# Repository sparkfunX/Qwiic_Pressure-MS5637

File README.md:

SparkFun Qwiic Pressure with MS5637
========================================

[*SparkX Pressure Sensor (Qwiic) - MS5637 (SPX-14688)*](https://www.sparkfun.com/products/14688)

MEMs based barometric pressure sensors are quite common these days. The Qwiic Pressure Sensor with the MS5637 shines by being the most sensitive barometric pressure sensor we have come across. It is capable of detecting the difference in 13cm of air! And the MS5637 is low cost and easy to use.

The Qwiic Pressure Sensor for the MS5637 is a very sensitive, fully calibrated, low power, easy to use barometric pressure sensor capable of detecting a change of as little as 13cm of air! The Qwiic Pressure Sensor is perfect for home weather stations, detecting changes in altitude, and pneumatic based switches or actuators.

The original manufacturer TE has written a great Arduino library for the device. We've added a heap of examples and new functions to make the sensor even easier to use. Search the Arduino Library manager for 'SparkFun MS5637' to get the latest library features.

SparkFun labored with love to create this code. Feel like supporting open source hardware? 
Buy a [breakout board](https://www.sparkfun.com/products/14688) from SparkFun!

Repository Contents
-------------------

* **/Documents** - Datasheets
* **/Hardware** - Eagle design files (.brd, .sch)

Library
--------------
* **[Arduino Library](https://github.com/sparkfun/SparkFun_MS5637_Arduino_Library)** - Library for reading pressure in mBar, altitude, etc.

License Information
-------------------

This product is _**open source**_! 

If you have any questions or concerns on licensing, please contact techsupport@sparkfun.com.

Please use, reuse, and modify these files as you see fit. Please maintain attribution to SparkFun Electronics and release any derivative under the same license.

Distributed as-is; no warranty is given.

- Your friends at SparkFun.

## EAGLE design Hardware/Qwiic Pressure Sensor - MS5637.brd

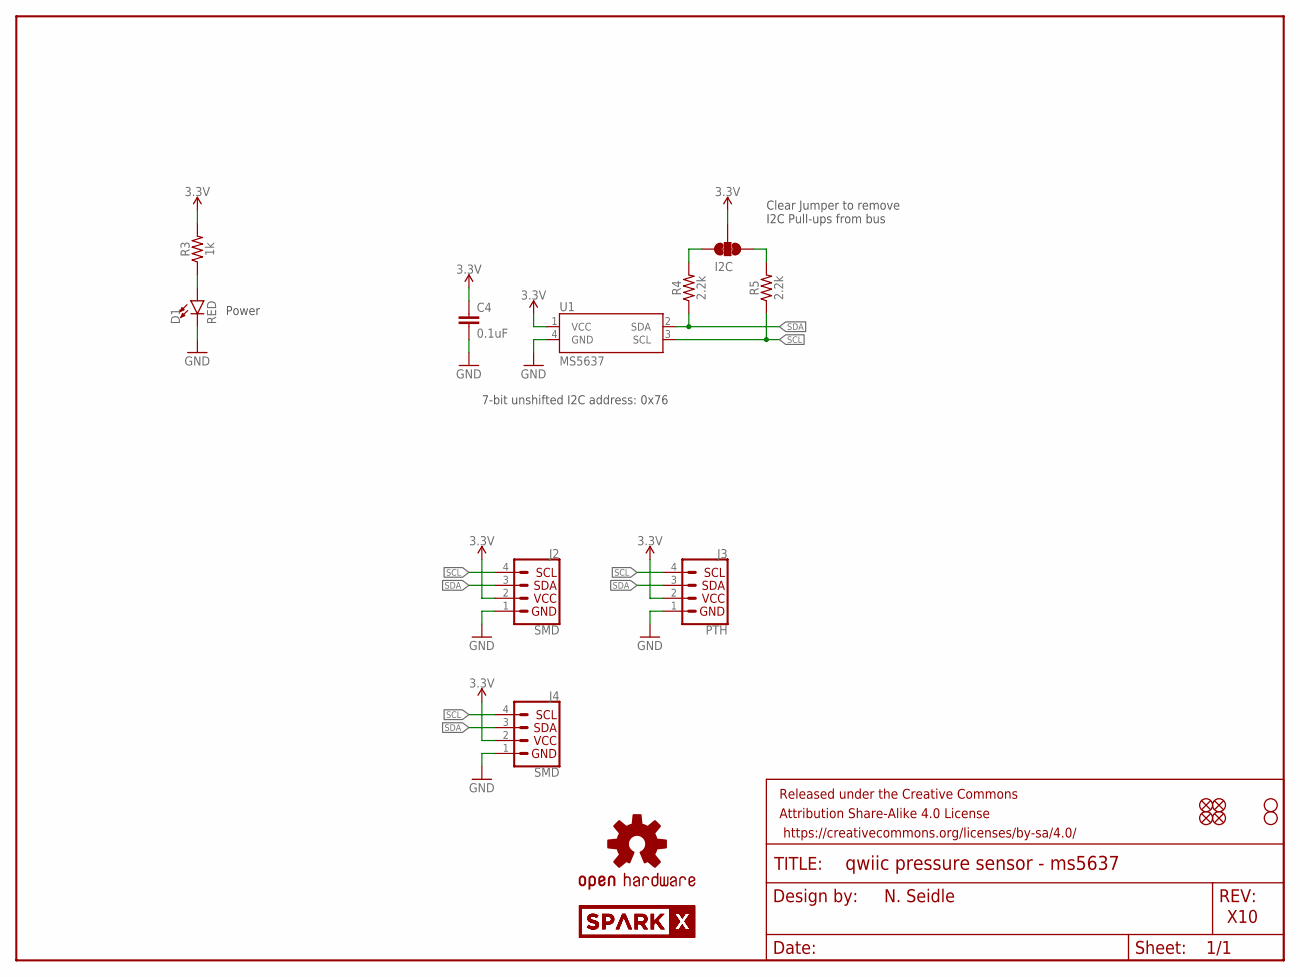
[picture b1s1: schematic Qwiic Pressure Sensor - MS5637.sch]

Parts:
C4: 0.1uF; 0603
D1: RED; LED-0603
FRAME1: FRAME-LETTER; CREATIVE_COMMONS
I2C: JUMPER-SMT_3_2-NC_TRACE_SILK; SMT-JUMPER_3_2-NC_TRACE_SILK
J2, J4: SMD; 1X04_1MM_RA
J3: PTH; 1X04_NO_SILK
JP1, JP2, JP5, JP6: FIDUCIALUFIDUCIAL; MICRO-FIDUCIAL
JP3, JP4: STAND-OFF
LOGO1: OSHW-LOGOMINI; OSHW-LOGO-MINI
R3: 1k; 0603
R4, R5: 2.2k; 0603
U1: MS5637
U$1, U$2: SPARKX-LOGO4; SPARKX-MEDIUM

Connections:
3.3V: C4.1, I2C.2, J2.2 (VCC), J3.2 (VCC), J4.2 (VCC), R3.2, U1.1 (VCC)
GND: C4.2, D1.C, J2.1 (GND), J3.1 (GND), J4.1 (GND), U1.4 (GND)
unnamed: I2C.1, R5.2
unnamed: I2C.3, R4.2
unnamed: D1.A, R3.1
SCL: J2.4 (SCL), J3.4 (SCL), J4.4 (SCL), R5.1, U1.3 (SCL)
SDA: J2.3 (SDA), J3.3 (SDA), J4.3 (SDA), R4.1, U1.2 (SDA)

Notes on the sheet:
N. Seidle
X10
7-bit unshifted I2C address: 0x76
Clear Jumper to remove I2C Pull-ups from bus
Power

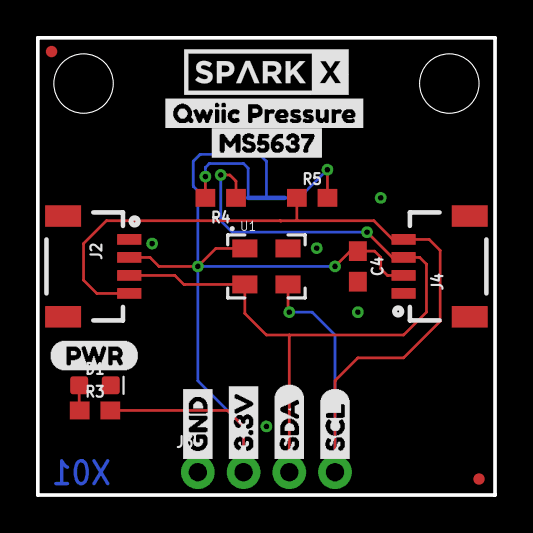
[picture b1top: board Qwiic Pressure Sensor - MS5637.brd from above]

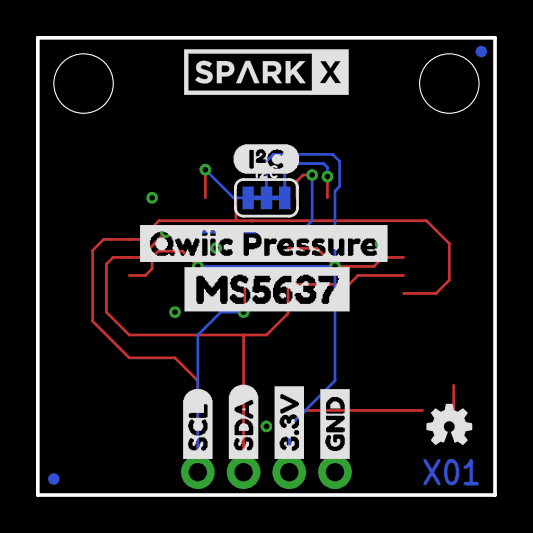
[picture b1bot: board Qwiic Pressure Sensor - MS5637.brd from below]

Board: 2 copper layers, 25.4 x 25.4 mm, 34 parts (12 on the bottom side), 7 nets.

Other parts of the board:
U$3, U$22: GND1
U$4, U$21: 3#3V2
U$5, U$27: SDA8
U$6, U$26: SCL9
U$7, U$14: MS56371
U$8, U$13: QWIIC_PRESSURE0
U$10: (PWR)
U$11: (I_SUPER2_C)

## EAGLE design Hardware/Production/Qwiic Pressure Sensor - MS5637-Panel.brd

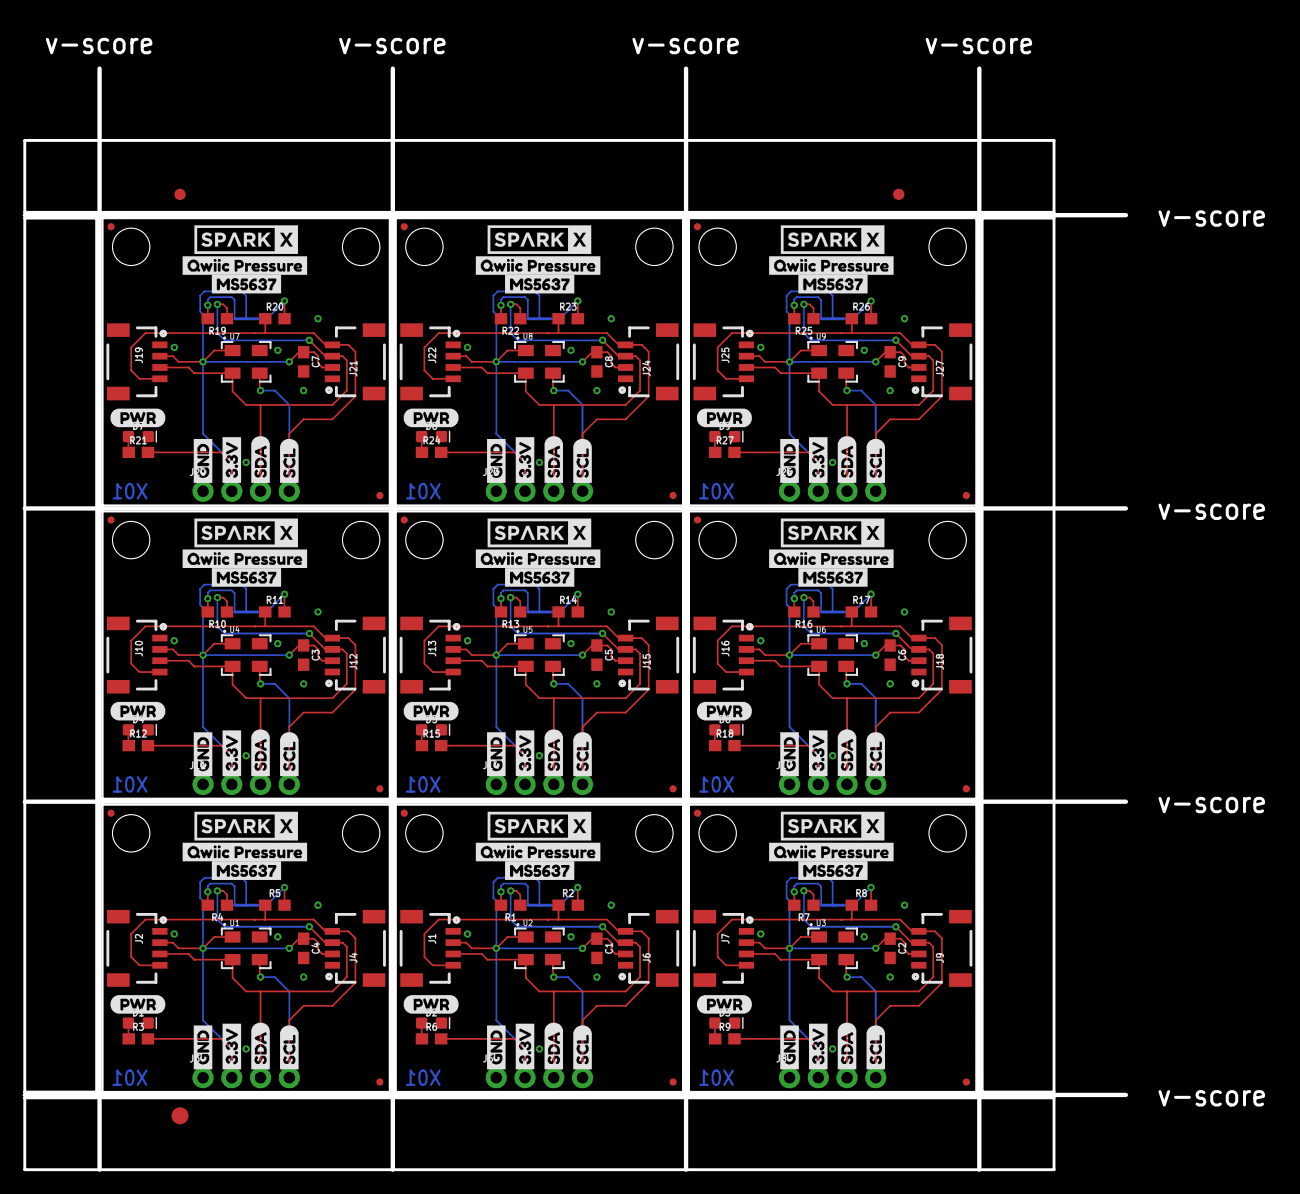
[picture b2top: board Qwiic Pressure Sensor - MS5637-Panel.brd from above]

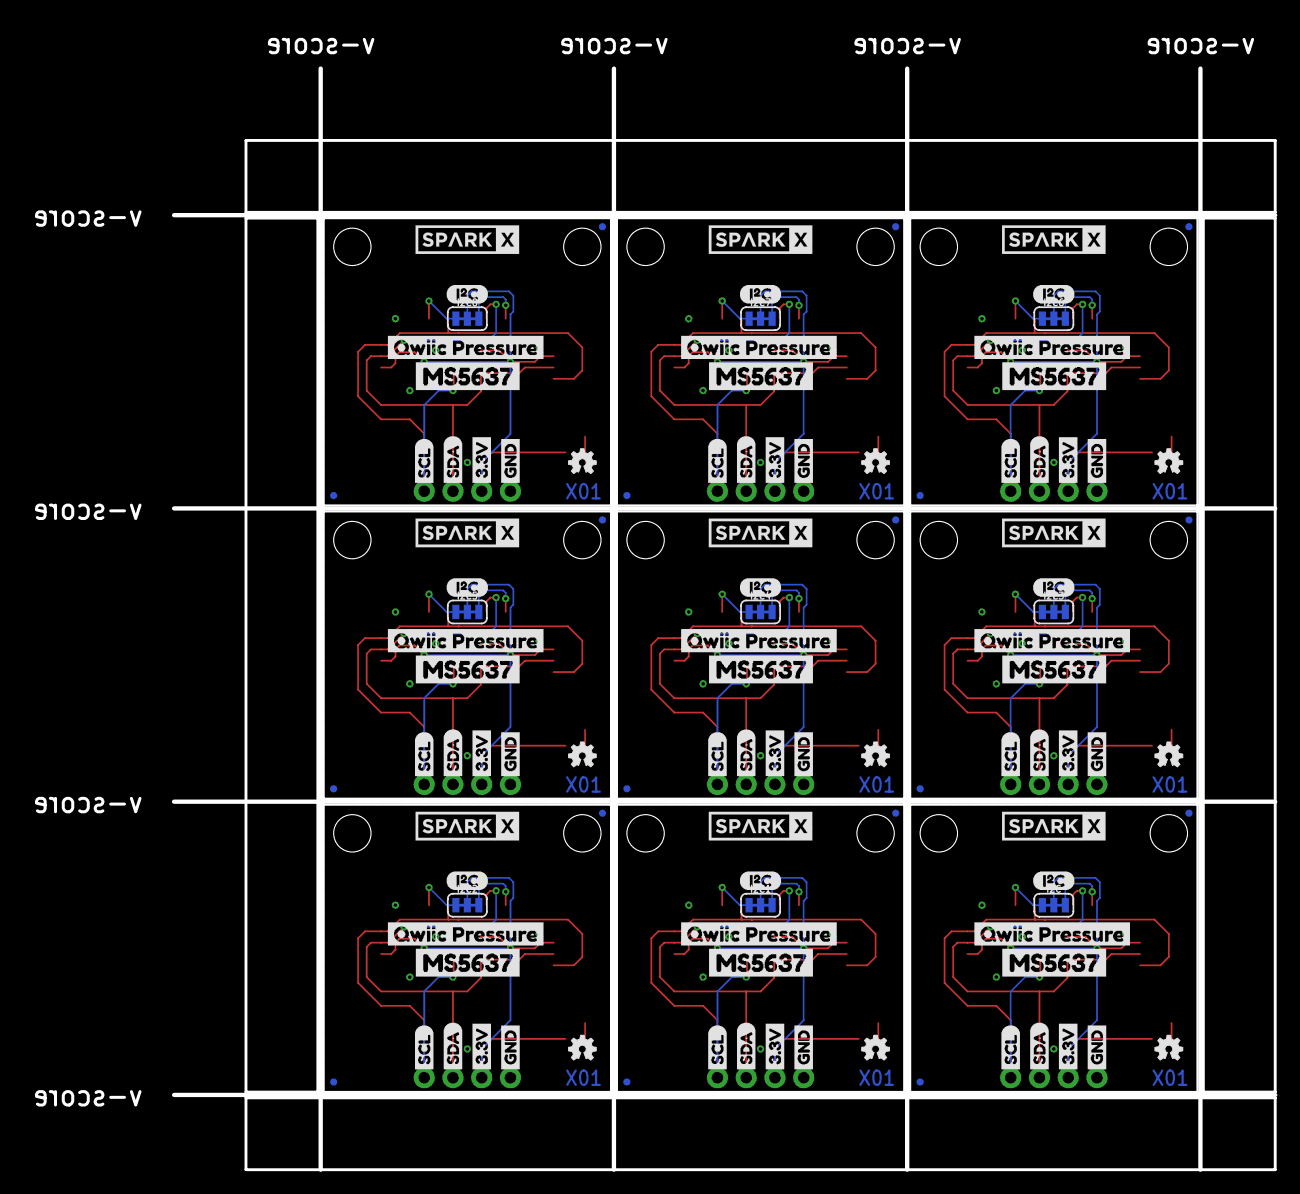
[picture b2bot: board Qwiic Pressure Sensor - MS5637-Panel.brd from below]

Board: 2 copper layers, 97.3 x 97.3 mm, 300 parts (108 on the bottom side), 63 nets.

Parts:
C1, C2, C3, C4, C5, C6, C7, C8, C9: 0.1uF; 0603
D1, D2, D3, D4, D5, D6, D7, D8, D9: RED; LED-0603
E$1, E$2: FIDUCIAL-1X2
E$3: FIDUCIAL-1.5X3
I2C, I2C1, I2C2, I2C3, I2C4, I2C5, I2C6, I2C7, I2C8: SMT-JUMPER_3_2-NC_TRACE_SILK
J1, J2, J4, J6, J7, J9, J10, J12, J13, J15, J16, J18, J19, J21, J22, J24, J25, J27: SMD; 1X04_1MM_RA
J3, J5, J8, J11, J14, J17, J20, J23, J26: PTH; 1X04_NO_SILK
JP1, JP2, JP5, JP6, JP9, JP10, JP11, JP12, JP15, JP16, JP17, JP18, JP21, JP22, JP23, JP24, JP27, JP28, JP29, JP30, JP33, JP34, JP35, JP36, JP39, JP40, JP41, JP42, JP45, JP46, JP47, JP48, JP51, JP52, JP53, JP54: FIDUCIALUFIDUCIAL; MICRO-FIDUCIAL
JP3, JP4, JP7, JP8, JP13, JP14, JP19, JP20, JP25, JP26, JP31, JP32, JP37, JP38, JP43, JP44, JP49, JP50: STAND-OFF
LOGO1, LOGO2, LOGO3, LOGO4, LOGO5, LOGO6, LOGO7, LOGO8, LOGO9: OSHW-LOGOMINI; OSHW-LOGO-MINI
R1, R2, R4, R5, R7, R8, R10, R11, R13, R14, R16, R17, R19, R20, R22, R23, R25, R26: 2.2k; 0603
R3, R6, R9, R12, R15, R18, R21, R24, R27: 1k; 0603
U1, U2, U3, U4, U5, U6, U7, U8, U9: MS5637
U$1, U$2, U$9, U$12, U$33, U$34, U$49, U$50, U$65, U$66, U$81, U$82, U$97, U$98, U$113, U$114, U$129, U$130: SPARKX-LOGO4; SPARKX-MEDIUM
U$3, U$16, U$19, U$22, U$36, U$39, U$52, U$55, U$68, U$71, U$84, U$87, U$100, U$103, U$116, U$119, U$132, U$135: GND1
U$4, U$15, U$20, U$21, U$35, U$40, U$51, U$56, U$67, U$72, U$83, U$88, U$99, U$104, U$115, U$120, U$131, U$136: 3#3V2
U$5, U$18, U$23, U$27, U$38, U$41, U$54, U$57, U$70, U$73, U$86, U$89, U$102, U$105, U$118, U$121, U$134, U$137: SDA8
U$6, U$17, U$24, U$26, U$37, U$42, U$53, U$58, U$69, U$74, U$85, U$90, U$101, U$106, U$117, U$122, U$133, U$138: SCL9
U$7, U$14, U$30, U$31, U$46, U$47, U$62, U$63, U$78, U$79, U$94, U$95, U$110, U$111, U$126, U$127, U$142, U$143: MS56371
U$8, U$13, U$29, U$32, U$45, U$48, U$61, U$64, U$77, U$80, U$93, U$96, U$109, U$112, U$125, U$128, U$141, U$144: QWIIC_PRESSURE0
U$10, U$25, U$43, U$59, U$75, U$91, U$107, U$123, U$139: (PWR)
U$11, U$28, U$44, U$60, U$76, U$92, U$108, U$124, U$140: (I_SUPER2_C)

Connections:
3.3V: C4.1, I2C.2, J2.2, J3.2, J4.2, R3.2, U1.1
3.3V1: C1.1, I2C1.2, J1.2, J5.2, J6.2, R6.2, U2.1
3.3V2: C2.1, I2C2.2, J7.2, J8.2, J9.2, R9.2, U3.1
3.3V3: C3.1, I2C3.2, J10.2, J11.2, J12.2, R12.2, U4.1
3.3V4: C5.1, I2C4.2, J13.2, J14.2, J15.2, R15.2, U5.1
3.3V5: C6.1, I2C5.2, J16.2, J17.2, J18.2, R18.2, U6.1
3.3V6: C7.1, I2C6.2, J19.2, J20.2, J21.2, R21.2, U7.1
3.3V7: C8.1, I2C7.2, J22.2, J23.2, J24.2, R24.2, U8.1
3.3V8: C9.1, I2C8.2, J25.2, J26.2, J27.2, R27.2, U9.1
GND: C4.2, D1.C, J2.1, J3.1, J4.1, U1.4
GND1: C1.2, D2.C, J1.1, J5.1, J6.1, U2.4
GND2: C2.2, D3.C, J7.1, J8.1, J9.1, U3.4
GND3: C3.2, D4.C, J10.1, J11.1, J12.1, U4.4
GND4: C5.2, D5.C, J13.1, J14.1, J15.1, U5.4
GND5: C6.2, D6.C, J16.1, J17.1, J18.1, U6.4
GND6: C7.2, D7.C, J19.1, J20.1, J21.1, U7.4
GND7: C8.2, D8.C, J22.1, J23.1, J24.1, U8.4
GND8: C9.2, D9.C, J25.1, J26.1, J27.1, U9.4
unnamed: I2C.1, R5.2
unnamed: I2C.3, R4.2
unnamed: D1.A, R3.1
unnamed: I2C1.1, R2.2
unnamed: I2C1.3, R1.2
unnamed: D2.A, R6.1
unnamed: I2C2.1, R8.2
unnamed: I2C2.3, R7.2
unnamed: D3.A, R9.1
unnamed: I2C3.1, R11.2
unnamed: I2C3.3, R10.2
unnamed: D4.A, R12.1
unnamed: I2C4.1, R14.2
unnamed: I2C4.3, R13.2
unnamed: D5.A, R15.1
unnamed: I2C5.1, R17.2
unnamed: I2C5.3, R16.2
unnamed: D6.A, R18.1
unnamed: I2C6.1, R20.2
unnamed: I2C6.3, R19.2
unnamed: D7.A, R21.1
unnamed: I2C7.1, R23.2
unnamed: I2C7.3, R22.2
unnamed: D8.A, R24.1
unnamed: I2C8.1, R26.2
unnamed: I2C8.3, R25.2
unnamed: D9.A, R27.1
SCL: J2.4, J3.4, J4.4, R5.1, U1.3
SCL1: J1.4, J5.4, J6.4, R2.1, U2.3
SCL2: J7.4, J8.4, J9.4, R8.1, U3.3
SCL3: J10.4, J11.4, J12.4, R11.1, U4.3
SCL4: J13.4, J14.4, J15.4, R14.1, U5.3
SCL5: J16.4, J17.4, J18.4, R17.1, U6.3
SCL6: J19.4, J20.4, J21.4, R20.1, U7.3
SCL7: J22.4, J23.4, J24.4, R23.1, U8.3
SCL8: J25.4, J26.4, J27.4, R26.1, U9.3
SDA: J2.3, J3.3, J4.3, R4.1, U1.2
SDA1: J1.3, J5.3, J6.3, R1.1, U2.2
SDA2: J7.3, J8.3, J9.3, R7.1, U3.2
SDA3: J10.3, J11.3, J12.3, R10.1, U4.2
SDA4: J13.3, J14.3, J15.3, R13.1, U5.2
SDA5: J16.3, J17.3, J18.3, R16.1, U6.2
SDA6: J19.3, J20.3, J21.3, R19.1, U7.2
SDA7: J22.3, J23.3, J24.3, R22.1, U8.2
SDA8: J25.3, J26.3, J27.3, R25.1, U9.2

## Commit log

2018-04-17 Adding datasheet. Adding readme.
2018-04-17 Readme update
2018-11-29 Add panel eagle file

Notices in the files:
parts and their libraries:
SparkFun-Resistors: Licensing: Creative Commons ShareAlike 4.0 International - https://creativecommons.org/licenses/by-sa/4.0
SparkFun-Aesthetics: Released under the Creative Commons Attribution Share-Alike 4.0 License
SparkFun-Aesthetics: https://creativecommons.org/licenses/by-sa/4.0
